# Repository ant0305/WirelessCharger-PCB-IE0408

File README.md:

# WirelessCharger-PCB-IE0408
Repositorio para el proyecto final del curso IE0408 sobre el diseño de una PCB de un cargador inalambrico. Contiene el circuito esquemático, el diseño de la PCB en *KiCad* y documentación sobre los componentes a utilizar, el procedimiento de diseño y otros detalles. 

Este repositorio y sus contenidos fueron diseñados durante el curso IE0408 durante el periodo II-2025 por los siguientes integrantes del equipo:

<div align="center">

|        **Integrantes**      | **Carné** | **Correo electrónico**|
|:---------------------------:|:---------:|:---------------------:|
|    Anthony Calvo García     |   C11433  |  anthonycalvo50@gmail.com |
|   Rodrigo Madrigal Montes   |   C24458  | rmadrigalmontes@gmail.com |

</div>

## Agradecimientos a  

El proyecto presentado fue posible gracias al valioso respaldo de **PCBWay**, a quienes deseamos extender nuestro más sincero agradecimiento. Las PCBs entregadas mostraron ser de una excelente calidad durante las pruebas realizadas, además de que el acabado en cada una de ellas es impecable, brindando exactamente el resultado que esperábamos.

Agradecemos, de igual manera, al equipo encargado de la atención al cliente, los cuales están siempre disponibles para brindar el apoyo solicitado de forma rápida y asertiva, lo que nos dio seguridad y tranquilidad durante todo el proceso de elaboración y entrega de las PCBs. 

### PCBs ensambladas 

Una vez recibidas las placas de PCBWay, se procedió con el ensamblaje manual de todos los componentes. A continuación se muestran imágenes del resultado:

<div align="center">

|  |
|:-----------------------------:|
|    *PCBs ensambladas y no ensambladas aún unidas*     |

</div>

<div align="center">

|  |
|:-----------------------------:|
|    *Vista lateral de las PCBs ensambladas unidas*     |

</div>

Una vez soldados todos los componentes en ambas PCBs se procedió a separarlas, rompiendo la uniones entre ambas como se muestra a continuación:

<div align="center">

|  |
|:-----------------------------:|
|    *Separación de ambas PCBs*     |

</div>

Y una vez separadas, lijando el sobrante de la junta de unión en ambas PCBs y agregando las bobinas el resultado final es el siguiente:

<div align="center">

|  |
|:-----------------------------:|
|    *Ambas PCBs ensambladas y separadas*     |

</div>

Nuevamente extendemos nuestros agradecimientos a **PCBWay** por apoyar a la realización de este proyecto. Recomendamos sus servicios para estudiantes, profesionales y cualquier persona interesada en manufacturar PCBs de alta calidad. Más información en [pcbway.com](https://www.pcbway.com).

### Lista de componentes

A continuación se incluye una lista con los componentes utilizados en el diseño, con el mismo número que se les asignó en el diseño final de PCB:

<div align="center">

| Componente | Valor / Modelo | Descripción / Función | Encapsulado |
|:---:|:---:|:---:|:---:|
| C1, C8 | 10uF, 2.2uF | Capacitor cerámico | (SMD) 1206 |
| C2, C3 | 100nF | Capacitor cerámico | (SMD) 1206 |
| C4, C5 | 10nF | Capacitor cerámico | (SMD) 1206 |
| C6, C7 | 2nF | Capacitor cerámico | (SMD) 1206 |
| D1, D2 | 1N4148 | Diodo Rectificador de alta velocidad | (THT) DO-35 |
| D3, D4, D5, D6 | SS14 | Diodo Schottky | (SMD) DO-214|
| J1, J2 | — | Terminal de tornillo (2 pines) | — | 
| L1, L2 | 1x02 (2.54mm) Female Header | Conectores para colocar las bobinas | — |
| Q1 | BD139 | Transistor NPN de potencia | (THT) TO-126 |
| Q2 | IRFZ44N | Transistor MOSFET de potencia | (THT) TO-220 |
| R1 | 100Ω | Resistor | (SMD) 1206 |
| R3 | 150Ω | Resistor | (SMD) 1206 |
| R2| 1kΩ | Resistor | (SMD) 1206 |
| RV1, RV2 | 1kΩ | Resistor variable/Potenciómetro, | (THT) 3296W |
| U1 | NE555D | Circuito Integrado Temporizador NE555 | (SMD) SOP8 |
| TP1, TP3, TP6 | 1x01 (2.54mm) Pin Header | Punto de prueba (Test Point) para Tierra (GND) | — |
| TP2 | 1x01 (2.54mm) Pin Header | Punto de prueba (Test Point) para medir la Salida del NE555 | — | 
| TP4 | 1x01 (2.54mm) Pin Header | Punto de prueba (Test Point) para medir la tensión del Receptor (RX) | — |
| TP5 | 1x01 (2.54mm) Pin Header | Punto de prueba (Test Point) para medir la tensión del Receptor (TX) | — | 

</div>

## Diseño de la PCB

Una vez simulado y definido el circuito final, se diseñó la PCB en *KiCad* con una arquitectura de **cuatro capas**, las cuales se distribuyen de la siguiente manera:

- **F.Cu**: Ruta de señales
- **In1.Cu**: Plano de alimentación +9V
- **In2.Cu**: Plano de tierra (GND)
- **B.Cu**: Ruta de señales

### Capas de la PCB

<div align="center">

|  |
|:-----------------------------:|
|    *Capa superior (F.Cu)*     |

</div>

<div align="center">

|  |
|:-----------------------------:|
|    *Capa inferior (B.Cu)*     |

</div>

<div align="center">

|  |
|:-------------------------------------------:|
|      *Capa interna 1 (In1.Cu)- +9V*         |

</div>

<div align="center">

|  |
|:-------------------------------------:|
|        *Capa interna (In2.Cu) - GND*         |

</div>

Además, se agregaron zonas de serigrafía, agujeros de montaje, así como textos identificativos y logotipos en el *silkscreen* con el nombre del proyecto y los autores. Como resultado final se muestra la PCB en el visor 3D de *KiCad* con y sin los modelos 3D 

<div align="center">

|  |
|:--:|
| *Vista 3D Frontal de la PCB en KiCad* |

</div>

<div align="center">

|  |
|:--:|
| *Vista 3D Frontal de la PCB en KiCad* |

</div>

<div align="center">

|  |
|:--:|
| *Vista 3D Frontal de la PCB en KiCad con modelos 3D* |

</div>

<div align="center">

|  |
|:--:|
| *Vista 3D Trasera de la PCB en KiCad con modelos 3D* |

</div>

<div align="center">

|  |
|:--:|
| *Vista 3D Lateral Izquierda de la PCB en KiCad con modelos 3D* |

</div>

## Diseño de una carcasa 3D

De forma adicional, se diseñó una carcasa 3D usando la herramienta FreeCAD que permite comprobar el correcto funcionamiento del prototipo y cómo cambia la cantidad de energía entregada dependiendo de la distancia entre el receptor y el emisor.

<div align="center">

|  |
|:--:|
| *Vista 3D de la carcasa diseñada para el emisor* |

</div>

<div align="center">

|  |
|:--:|
| *Vista 3D de la carcasa diseñada para el receptor* |

</div>

<div align="center">

|  |
|:--:|
| *Unión del emisor y receptor usando la carcasa diseñada* |

</div>

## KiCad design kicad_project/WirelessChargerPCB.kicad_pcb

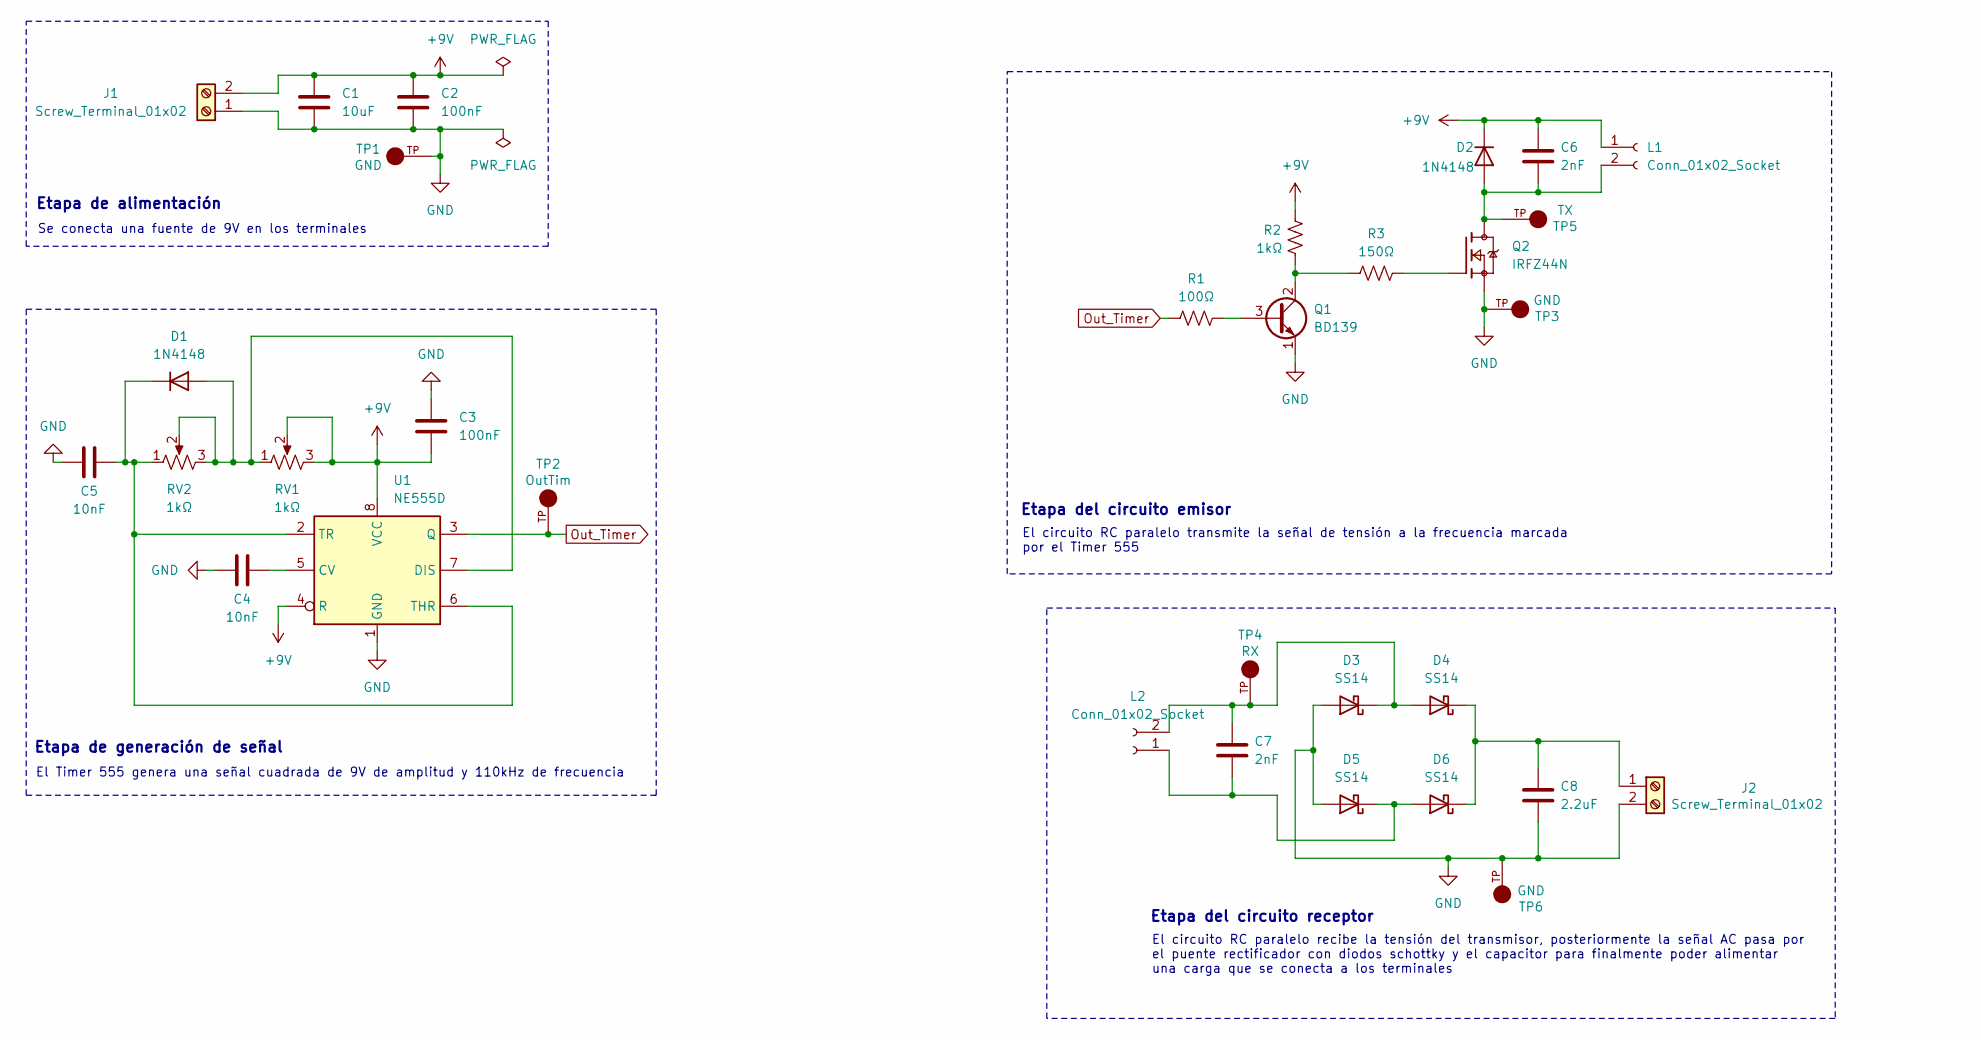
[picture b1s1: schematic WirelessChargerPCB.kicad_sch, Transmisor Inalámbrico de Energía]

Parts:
C1: 10uF; C_1206_3216Metric
C2, C3: 100nF; C_1206_3216Metric
C4, C5: 10nF; C_1206_3216Metric
C6, C7: 2nF; C_1206_3216Metric
C8: 2.2uF; C_1206_3216Metric
D1, D2: 1N4148; D_DO-35_SOD27_P7.62mm_Horizontal
D3, D4, D5, D6: SS14; D_SMA
J1, J2: Screw_Terminal_01x02; TerminalBlock_bornier-2_P5.08mm
L1, L2: Conn_01x02_Socket; PinSocket_1x02_P2.54mm_Vertical
Q1: BD139; TO-126-3_Vertical
Q2: IRFZ44N; TO254P1016X419X2286-3; PARTREV 09/21/10
R1: 100Ω; R_1206_3216Metric
R2: 1kΩ; R_1206_3216Metric
R3: 150Ω; R_1206_3216Metric
RV1, RV2: 1kΩ; Potentiometer_Bourns_3296W_Vertical
TP1, TP3, TP6: GND; KEYSTONE_5263; PARTREV H
TP2: OutTim; KEYSTONE_5263; PARTREV H
TP4: RX; KEYSTONE_5263; PARTREV H
TP5: TX; KEYSTONE_5263; PARTREV H
U1: NE555D; SOIC-8_3.9x4.9mm_P1.27mm

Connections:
+9V: C1.1, C2.1, C3.2, C6.1, D2.1 (K), J1.2, L1.1, R2.2, RV1.2, RV1.3, U1.4 (R), U1.8 (VCC)
GND: C1.2, C2.2, C3.1, C4.1, C5.1, C8.2, D3.2 (A), D5.2 (A), J1.1, J2.2, Q1.1 (E), Q2.3, TP1.TP, TP3.TP, TP6.TP, U1.1 (GND)
unnamed: D1.2 (A), RV1.1, RV2.2, RV2.3, U1.7 (DIS)
unnamed: C5.2, D1.1 (K), RV2.1, U1.2 (TR), U1.6 (THR)
unnamed: C6.2, D2.2 (A), L1.2, Q2.2, TP5.TP
unnamed: C7.1, D3.1 (K), D4.2 (A), L2.2, TP4.TP
unnamed: C8.1, D4.1 (K), D6.1 (K), J2.1
unnamed: C7.2, D5.1 (K), D6.2 (A), L2.1
unnamed: Q1.3 (B), R1.2
unnamed: Q1.2 (C), R2.1, R3.1
unnamed: Q2.1, R3.2
unnamed: C4.2, U1.5 (CV)
Out_Timer: R1.1, TP2.TP, U1.3 (Q)

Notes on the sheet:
El Timer 555 genera una señal cuadrada de 9V de amplitud y 110kHz de frecuencia
Etapa de generación de señal
Etapa del circuito emisor
Etapa de alimentación
El circuito RC paralelo recibe la tensión del transmisor, posteriormente la señal AC pasa por el puente rectificador con diodos schottky y el capacitor para finalmente poder alimentar una carga que se conecta a los terminales
El circuito RC paralelo transmite la señal de tensión a la frecuencia marcada por el Timer 555
Se conecta una fuente de 9V en los terminales
Etapa del circuito receptor

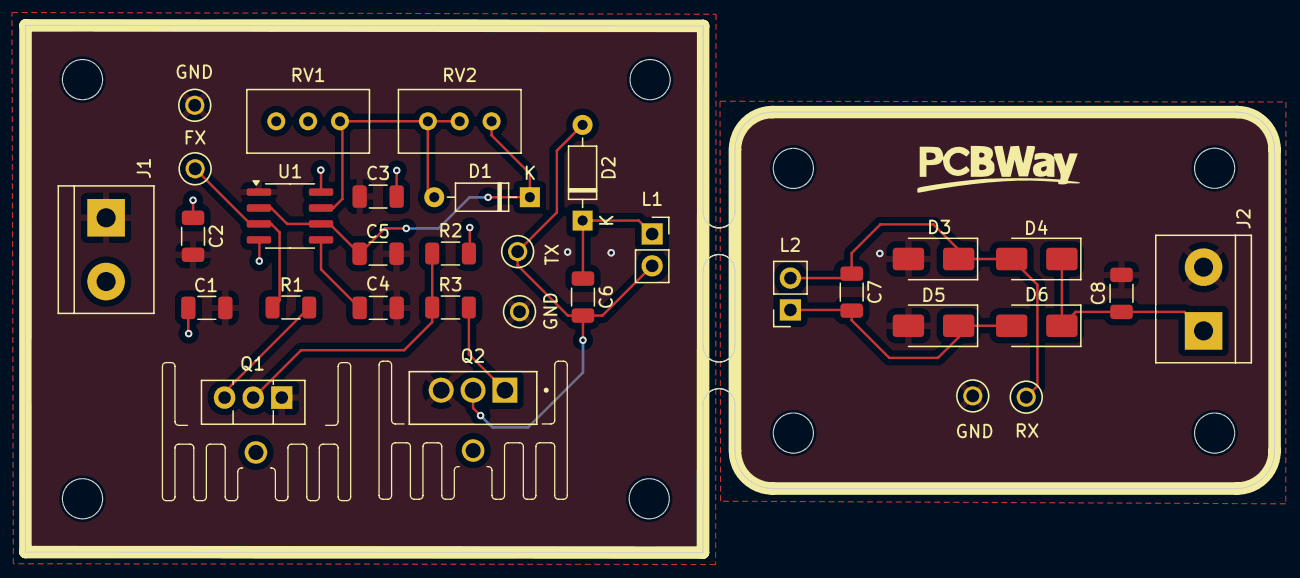
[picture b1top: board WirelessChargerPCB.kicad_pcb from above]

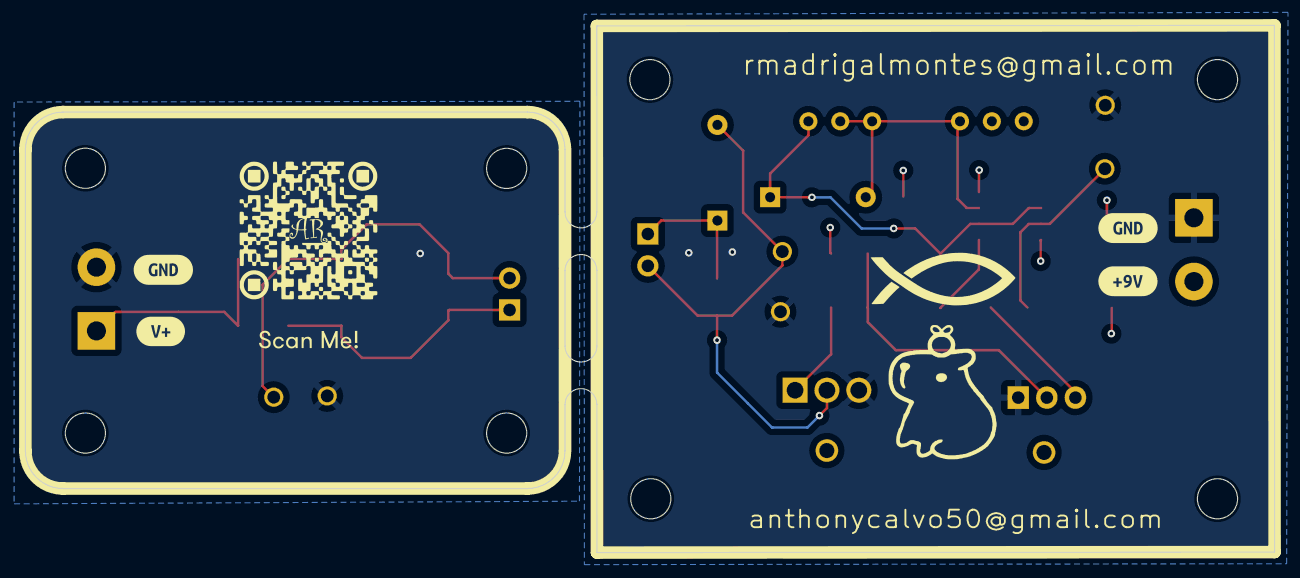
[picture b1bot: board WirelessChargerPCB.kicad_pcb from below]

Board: 4 copper layers, 99.5 x 42.0 mm, 38 parts (4 on the bottom side), 13 nets.

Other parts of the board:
kibuzzard-69159BA1: G***; kibuzzard-69159BA1
kibuzzard-69159BFD: G***; kibuzzard-69159BFD
kibuzzard-69159C7D: G***; kibuzzard-69159C7D
kibuzzard-69159C9A: G***; kibuzzard-69159C9A
mouse-bite-2.54mm-slot, mouse-bite-2.54mm-slot#2: VAL**; mouse-bite-2.54mm-slot

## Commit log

2025-11-06 Agregando archivos del proyecto de la PCB en KiCad
2025-11-06 Agregando nombre de los integrantes al README.md
2025-11-12 Agregando huellas y modelos 3D, además de otros cambios en el editor de placas y esquemático
2025-11-13 Agregando huellas de Heatsinks y relizando acomodo de ambas PCBs
2025-11-13 Ruteando y agregando detalles en Silkscreen en ambas PCBs
2025-11-15 Agregando informacion importante al silkcreem ademas del agujero de montaje para el disipador asi como una reconfiguracion a la placa del circuito transmisor
2025-11-15 Agregando mouse-bites y logos en ambas PCBs
2025-11-15 Agregando imagenes de la PCB en KiCad
2025-11-15 Recortando imagenes de las vistas 3D de las PCBs
2025-11-15 Agregando archivos de fabricacion en el directorio outputs/
2025-11-19 Agregando una conexion faltante en el esquematico y actualizando el editor de placas
2025-12-03 Agregando nuevos puntos de prueba y corrigiendo +9V faltante
2025-12-03 Agregando nuevos archivos de fabricacion
2025-12-06 Agregando parte de la documentacion del proyecto
2025-12-07 Corrigiendo un error en la ultima imagen
2025-12-10 Agregando sección de agradecimientos a PCBWay en el README.md
2025-12-10 Agregando imagen del logo de PCBWay en el README.md
2025-12-10 Ajustando logo de PCBWay en el README.md
    Ajustando logo de PCBWay en el README.md
2026-06-01 Agregando la documentación respecto a la implementación 3D diseñada
2026-06-01 Agregando los archivos de fabricación de la implementación 3D diseñada
